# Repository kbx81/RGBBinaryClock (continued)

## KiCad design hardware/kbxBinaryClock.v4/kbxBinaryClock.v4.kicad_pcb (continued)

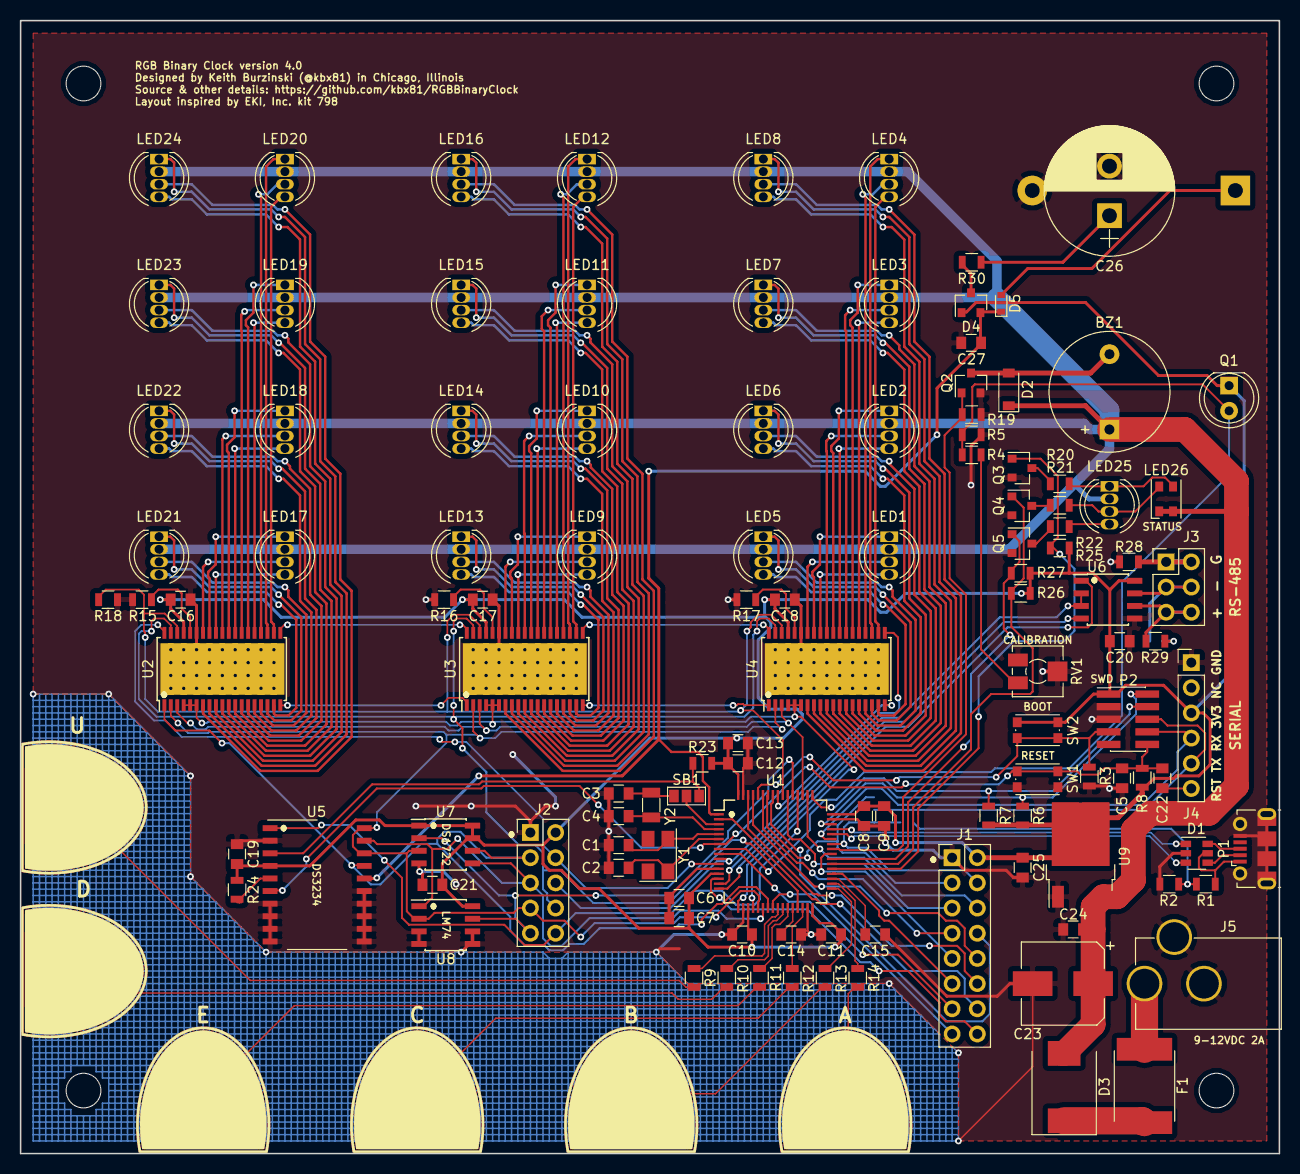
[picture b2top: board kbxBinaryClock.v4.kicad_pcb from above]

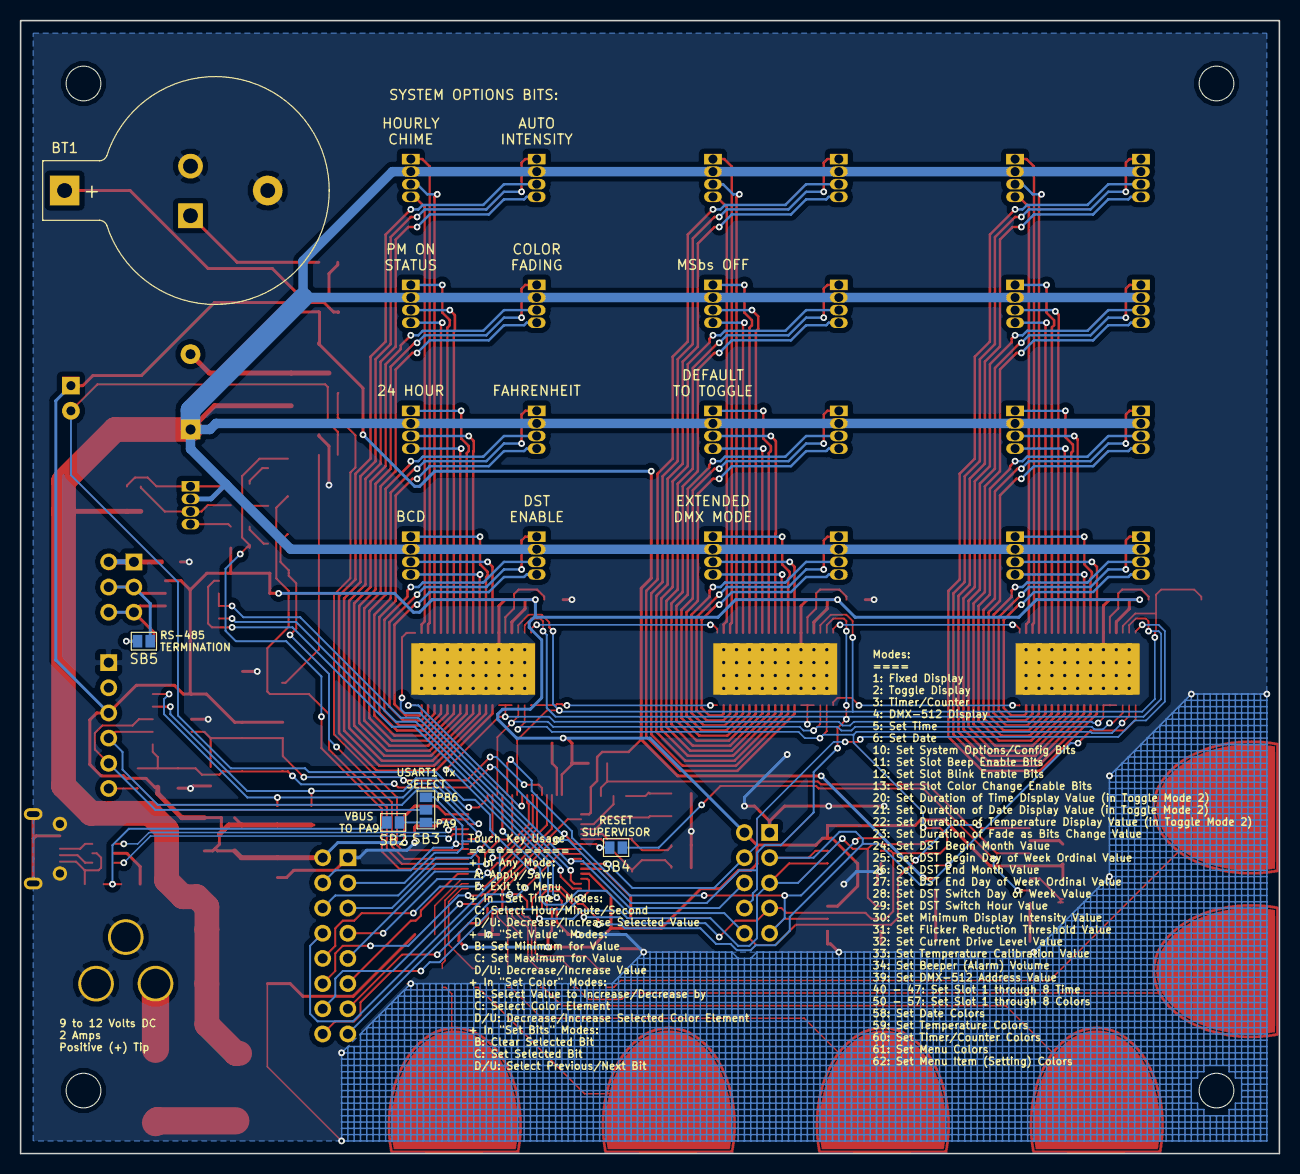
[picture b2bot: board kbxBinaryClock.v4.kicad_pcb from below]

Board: 2 copper layers, 127.0 x 114.3 mm, 132 parts (5 on the bottom side), 169 nets.

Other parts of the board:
MH1, MH2, MH3, MH4: MountingHole_3.5mm

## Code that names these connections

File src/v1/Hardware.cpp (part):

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//
static bool _adcSampleRefreshNow = false;

// state of the XBLNK pin
//
static bool _displayBlankingState = false;

// indicates to setDisplayBlankPin() that it should NOT clear the BLANK pin as
//  a display write is in progress with flicker reduction active
volatile static bool _displayBlankForWrite = false;

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  {
    // Configure current drive control pins
    gpio_mode_setup(cCurrentDrivePort, GPIO_MODE_OUTPUT, GPIO_PUPD_NONE, cCurrentDriveLowPin | cCurrentDriveHighPin);
    // Configure the SPI NSS and BLANK pins for the LED drivers
    gpio_mode_setup(cNssPort, GPIO_MODE_OUTPUT, GPIO_PUPD_NONE, cNssDisplayPin | cBlankDisplayPin);
    // gpio_mode_setup(cBlankDisplayPort, GPIO_MODE_OUTPUT, GPIO_PUPD_NONE, cBlankDisplayPin);
    // Configure the buzzer output
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  {
    // Configure current drive control pins
    gpio_mode_setup(cCurrentDrivePort, GPIO_MODE_OUTPUT, GPIO_PUPD_NONE, cCurrentDriveLowPin | cCurrentDriveHighPin);
    // Configure the SPI NSS and BLANK pins for the LED drivers
    gpio_mode_setup(cNssPort, GPIO_MODE_OUTPUT, GPIO_PUPD_NONE, cNssDisplayPin | cBlankDisplayPin);
    // gpio_mode_setup(cBlankDisplayPort, GPIO_MODE_OUTPUT, GPIO_PUPD_NONE, cBlankDisplayPin);
    // Configure the analog input pin for the phototransistor
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    gpio_mode_setup(cCurrentDrivePort, GPIO_MODE_OUTPUT, GPIO_PUPD_NONE, cCurrentDriveLowPin | cCurrentDriveHighPin);
    // Configure the SPI NSS pins for the LED drivers, RTC, and temp sensor
    gpio_mode_setup(cNssPort, GPIO_MODE_OUTPUT, GPIO_PUPD_NONE, cNssDisplayPin | cNssRtcPin | cNssTemperaturePin);
    // Configure the BLANK pin for the LED drivers
    gpio_mode_setup(cBlankDisplayPort, GPIO_MODE_OUTPUT, GPIO_PUPD_NONE, cBlankDisplayPin);
    // Configure the analog input pin for the phototransistor
    gpio_mode_setup(cPhototransistorPort, GPIO_MODE_ANALOG, GPIO_PUPD_NONE, cPhototransistorPin);
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  {
    // Configure the SPI NSS pins for the LED drivers, RTC, and temp sensor
    gpio_mode_setup(cNssPort, GPIO_MODE_OUTPUT, GPIO_PUPD_NONE, cNssDisplayPin | cNssRtcPin | cNssTemperaturePin);
    // Configure the BLANK pin for the LED drivers
    gpio_mode_setup(cBlankDisplayPort, GPIO_MODE_OUTPUT, GPIO_PUPD_NONE, cBlankDisplayPin);
    // Configure the analog input pin for the phototransistor
    gpio_mode_setup(cPhototransistorPort, GPIO_MODE_ANALOG, GPIO_PUPD_NONE, cPhototransistorPin);
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
void _i2cSetup()
{
  // Configure GPIOs SCL=PB8 and SDA=PB9 so we can reset the bus nicely
  gpio_mode_setup(cI2c1Port, GPIO_MODE_OUTPUT, GPIO_PUPD_PULLUP, cI2c1SlcPin | cI2c1SdaPin);
  gpio_set_output_options(cI2c1Port, GPIO_OTYPE_OD, GPIO_OSPEED_100MHZ, cI2c1SlcPin | cI2c1SdaPin);

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      case SpiPeripheral::LedDriversOther:
        // Configure other peripherals MISO pin as input
        gpio_mode_setup(cSpi1Port, GPIO_MODE_INPUT, GPIO_PUPD_NONE, cSpi1MisoPin);
        // MISO=PB4 from LED drivers
        gpio_mode_setup(cSpi1AltPort, GPIO_MODE_AF, GPIO_PUPD_NONE, cSpi1MisoDisplayPin);
        // LED drivers can cope with a higher clock rate
        // spi_set_baudrate_prescaler(SPI1, SPI_CR1_BAUDRATE_FPCLK_DIV_4);
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      default:
        // Configure display driver peripheral MISO pin as input
        gpio_mode_setup(cSpi1AltPort, GPIO_MODE_INPUT, GPIO_PUPD_NONE, cSpi1MisoDisplayPin);
        // Configure GPIOs: SCK=PA5, MISO=PA6 and MOSI=PA7
        gpio_mode_setup(cSpi1Port, GPIO_MODE_AF, GPIO_PUPD_NONE, cSpi1MisoPin);
        // RTC/Temp sensor technically require a slower clock rate...
        // ...but they seem to work with the same fast rate as the LED drivers...
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{
  // Setup SPI1 pins as alternate function zero
  gpio_set_af(cSpi1Port, GPIO_AF0, cSpi1SckPin | cSpi1MisoPin | cSpi1MosiPin);
  // MISO=PB4 from LED drivers
  gpio_set_af(cSpi1AltPort, GPIO_AF0, cSpi1MisoDisplayPin);

  // Configure GPIOs: SCK=PA5 and MOSI=PA7
  gpio_mode_setup(cSpi1Port, GPIO_MODE_AF, GPIO_PUPD_NONE, cSpi1SckPin | cSpi1MosiPin);

  // Reset SPI, SPI_CR1 register cleared, SPI is disabled
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}


void blinkStatusLed(const RgbLed led1, const RgbLed led2, uint32_t numberOfBlinks, const uint32_t delayLength)
{
  // be sure this is off so blinking is visible
  DisplayManager::setStatusLedAutoRefreshing(false);
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
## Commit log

2018-02-11 Quick minimal copy update
2018-02-17 Initial v2 source commit
2018-02-18 Modified PCBs to accommodate a 16mm buzzer element
2018-02-18 Added BoM, hw README, PCB tweaks
2018-02-18 Fix hw README formatting
2018-02-18 HW README copy fixes
2018-02-18 BoM fix
2018-02-18 More copy fixes
2018-02-20 Added support for reading the LM75
2018-02-22 Status LED tweaks, performance tweaks
2018-03-01 Part numbering fix
2018-03-03 Lots of clean-up and fixes
2018-03-03 Added disconnect on DS323x reset line
2018-03-03 Updated gerbers
2018-03-07 Initial v3 source commit
2018-03-09 Updated/added gerbers
2018-03-13 All sorts of tweaks/fixes/additions
2018-03-17 Backports to v1/v2
2018-03-18 SetTimeDateView can display AM/PM on status LED
2018-03-19 Added simple volume control and RTC not set menu guidance
2018-03-20 Updated Silkscreen for volume mode and added clearer pin 1 markings for ICs
2018-03-20 Remove files
2018-03-22 LM74 support implemented
2018-03-22 More color customizations, fixes, binaries
2018-03-23 Cleaned up temp sensor APIs
2018-03-31 Added MSOP footprint for temp sensor
2018-04-01 Updated slikscreen, minor tweaks
2018-04-01 Initial commit to branch
2018-04-03 Everything DMA and I2C works properly now
2018-04-10 Proper MCP9808 support, other fixes and tweaks
2018-05-25 DMX-512 control implemented
2018-05-25 Documentation formatting fixes
2018-05-27 Smoothed out automagic display intensity adjustments
2018-05-28 Squashed a display bug, some other tweaks
2018-05-28 Copy updates
2018-05-30 DMX-512 receiver and control tweaks
2018-06-01 Improved SetColorsView, other tweaks, optimizations
2018-06-06 Various tweaks/fixes/optimizations
2018-06-07 Minor DMX-512 controller fixes, tweaks, clean-up
2018-06-10 General clean-up, tweaks, and fixes
2018-06-10 BoM separation by hw version, markdown versions added
2018-06-10 BoM formatting fix
2018-06-10 BoM copy fix
2018-06-10 Copy update
2018-06-11 Attached CC-BY-SA to hardware
2018-06-11 Copy fix
2018-06-11 Copy update regarding heat
2018-11-26 Initial v4 hw & sw commit
2018-11-26 Copy fixes
2018-12-09 Various tweaks and fixes
2018-12-20 Consolidated sources, tons of other optimizations
2019-01-03 Various fixes, improvements, and clean-up
2019-01-03 Updated for KiCad v5, updated silks
2019-01-05 Implemented manual brightness control
2019-01-09 AlarmHandler reworked, date format added, other fixes
2019-01-09 Added/revised project documentation
2019-02-09 Refactored SetTimeDateView
2019-02-09 Clean-up of some DMA code for readability
2019-02-10 Clean-up of some hardware code for readability
